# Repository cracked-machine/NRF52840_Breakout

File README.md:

### NRF52840 Breakout Board

Simple dev board for NRF52840 MCU, breaks out all pins to the board.

Antenna options to be confirmed.

#### Schematic

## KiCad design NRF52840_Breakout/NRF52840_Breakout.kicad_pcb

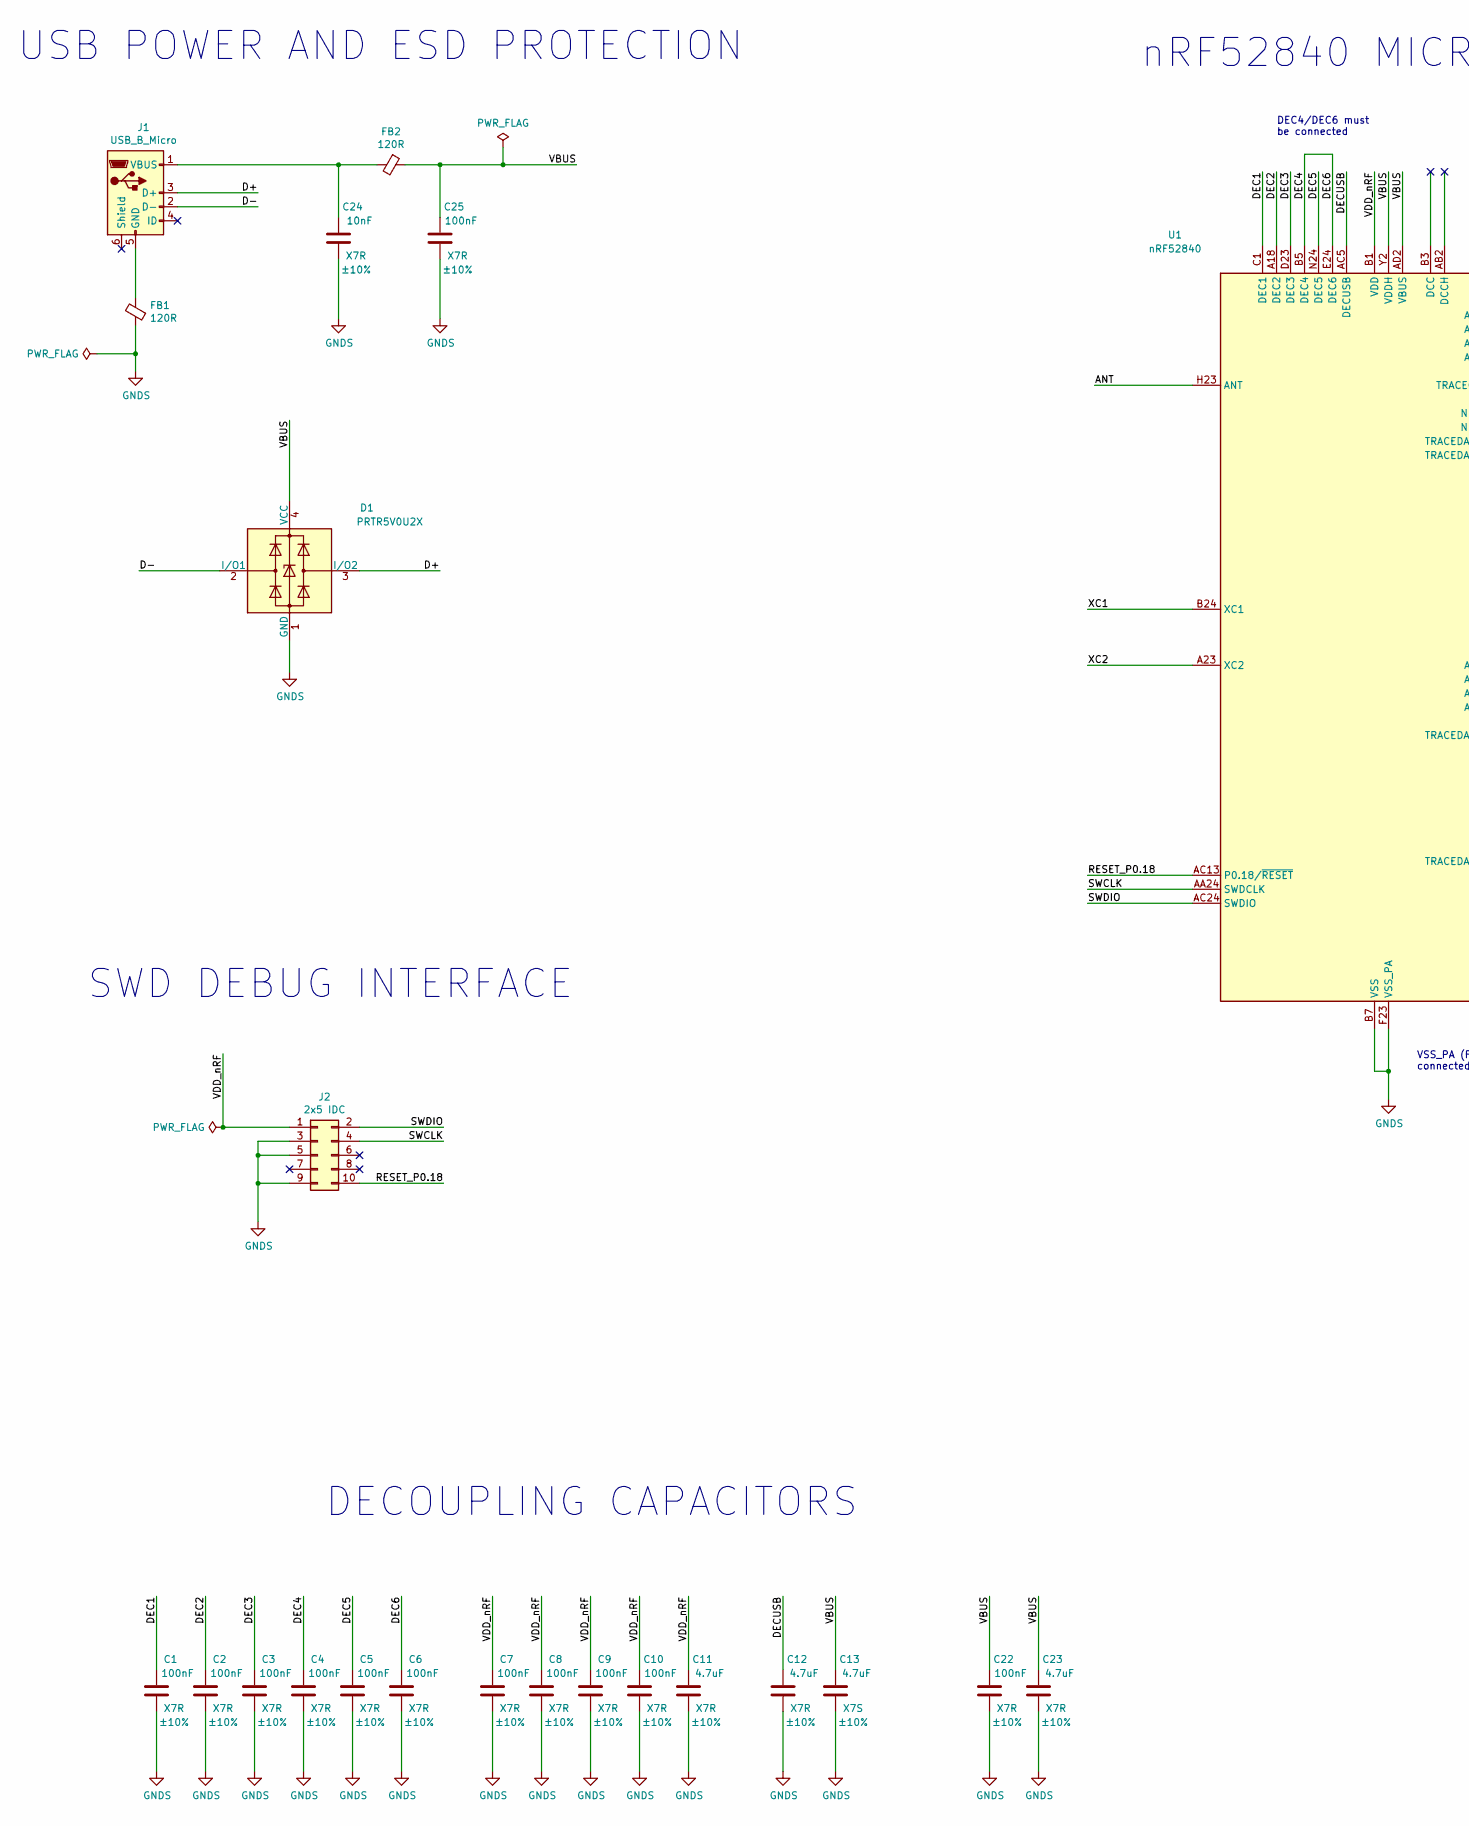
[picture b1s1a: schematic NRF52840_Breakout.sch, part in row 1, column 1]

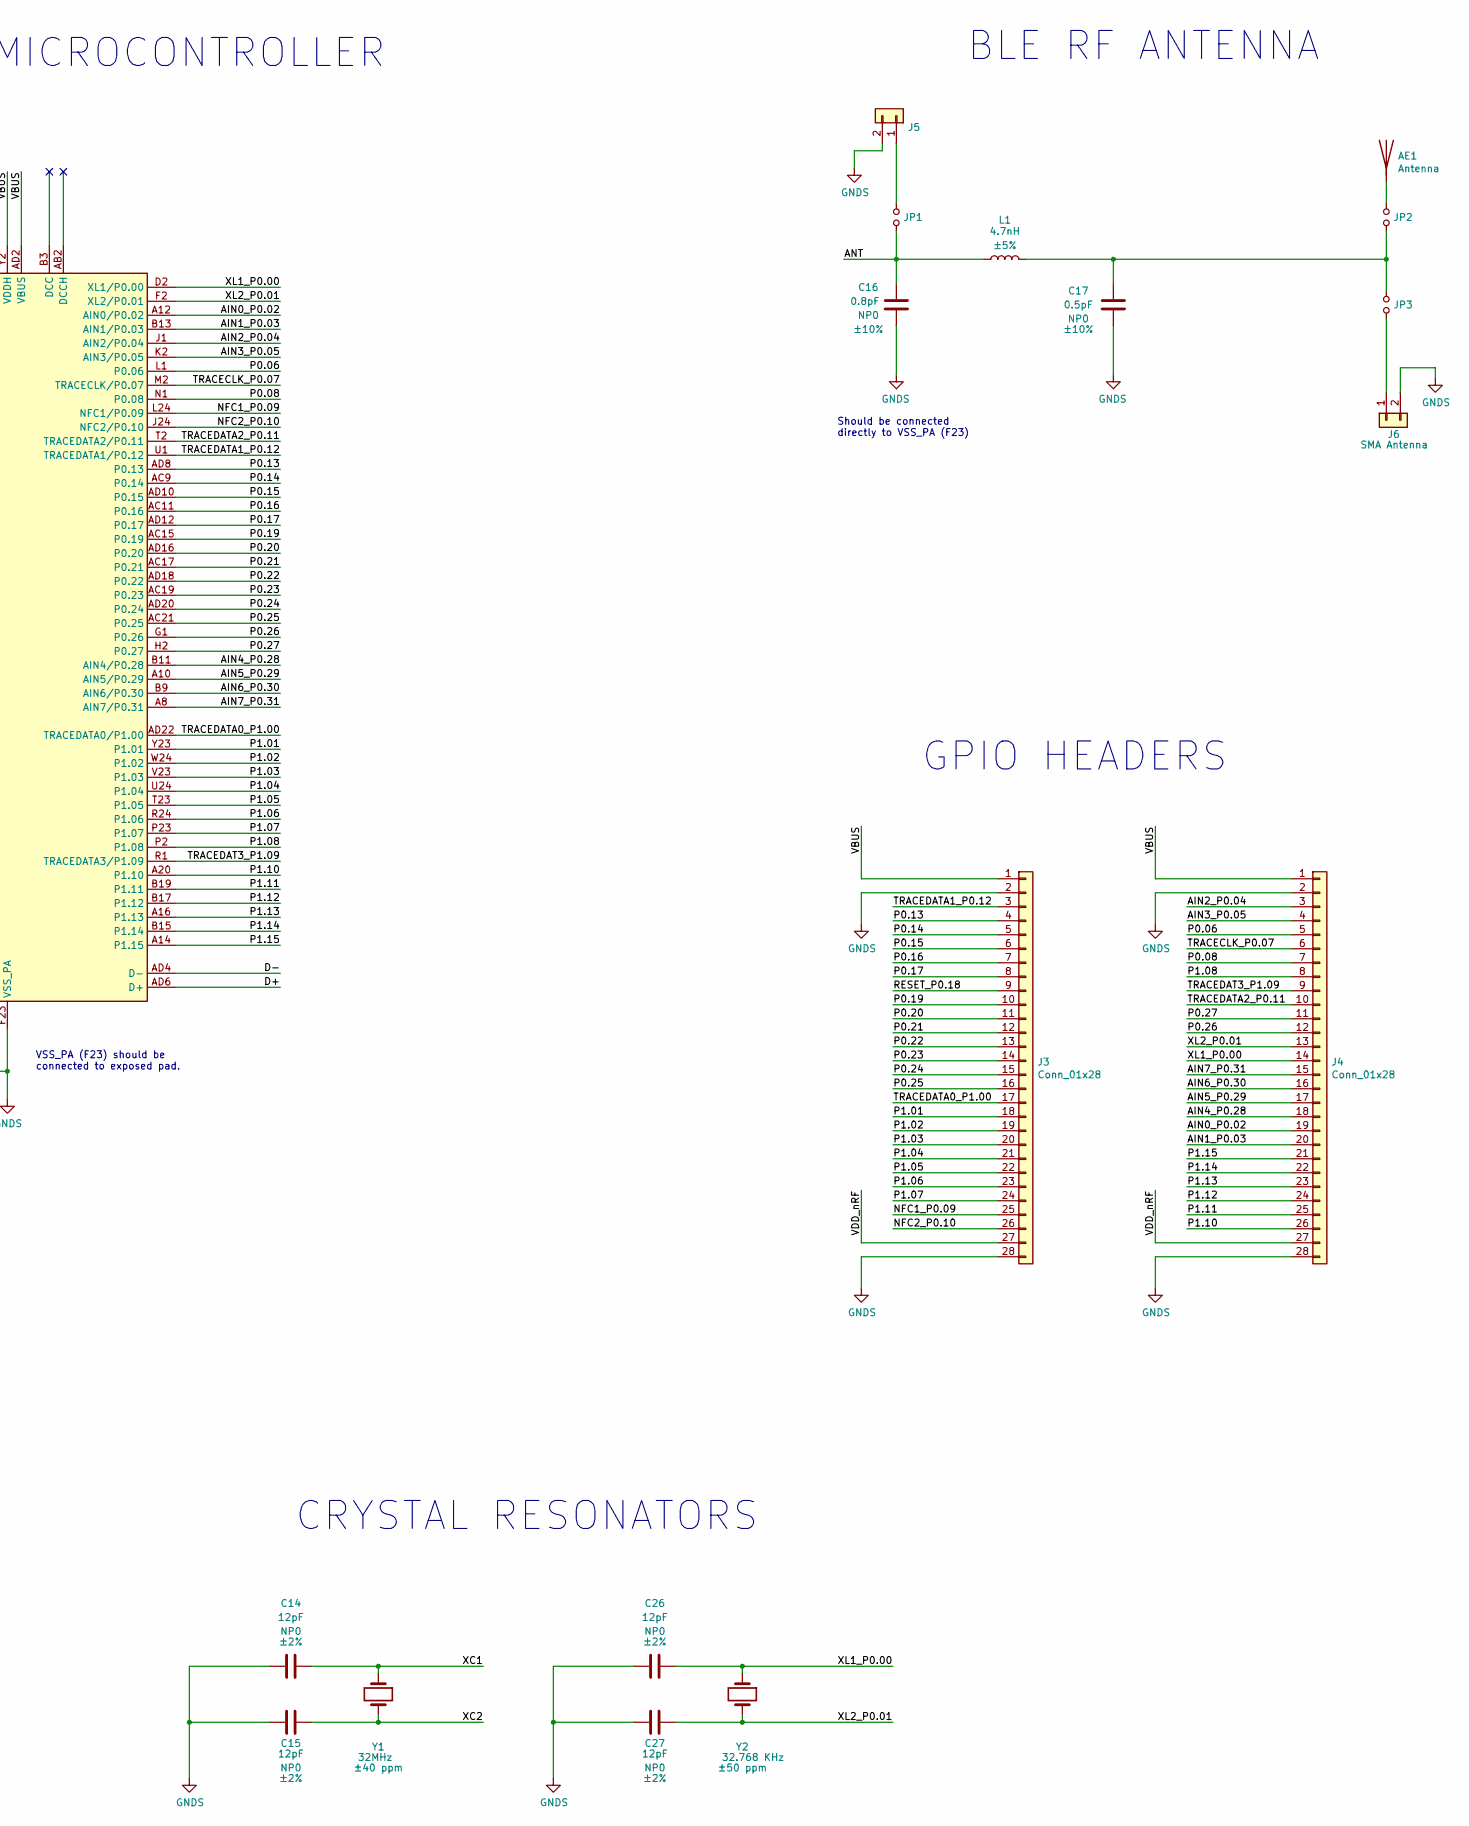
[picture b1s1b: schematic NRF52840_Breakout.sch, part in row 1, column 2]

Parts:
AE1: Antenna; Nordic_2_4GHz_Meander_RightSided
C1, C2, C3, C4, C5, C6, C7, C8, C9, C10, C22, C25: 100nF; C_0402_1005Metric_Pad0.74x0.62mm_HandSolder; Tolerance ±10%
C11, C12, C23: 4.7uF; C_0402_1005Metric_Pad0.74x0.62mm_HandSolder; Tolerance ±10%
C13: 4.7uF; C_0603_1608Metric_Pad1.08x0.95mm_HandSolder; Tolerance ±10%
C14, C15, C26, C27: 12pF; C_0402_1005Metric_Pad0.74x0.62mm_HandSolder; Tolerance ±2%
C16: 0.8pF; C_0402_1005Metric_Pad0.74x0.62mm_HandSolder; Tolerance ±10%
C17: 0.5pF; C_0402_1005Metric_Pad0.74x0.62mm_HandSolder; Tolerance ±10%
C24: 10nF; C_0402_1005Metric_Pad0.74x0.62mm_HandSolder; Tolerance ±10%
D1: PRTR5V0U2X; SOT-143
FB1, FB2: 120R; L_0402_1005Metric_Pad0.77x0.64mm_HandSolder
J1: USB_B_Micro; USB_Micro-B_Molex-105017-0001
J2: 2x5 IDC; PinHeader_2x05_P1.27mm_Vertical_SMD
J3, J4: Conn_01x28; PinHeader_1x28_P2.54mm_Vertical
J5: Conn_01x02; MMCX_Molex_73415-1471_Vertical
J6: SMA Antenna; MMCX_Molex_73415-1471_Vertical
JP1, JP2, JP3: Jumper_NO_Small; C_0402_1005Metric_Pad0.74x0.62mm_HandSolder
L1: 4.7nH; L_0402_1005Metric_Pad0.77x0.64mm_HandSolder; Tolerance ±5%
U1: nRF52840; Nordic_AQFN-73-1EP_7x7mm_P0.5mm
Y1: 32MHz; Crystal_SMD_2016-4Pin_2.0x1.6mm; Tolerance ±40 ppm
Y2: 32.768 KHz; Crystal_SMD_3215-2Pin_3.2x1.5mm; Tolerance ±50 ppm

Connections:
/AIN0_P0.02: J4.19, U1.A12 (AIN0/P0.02)
/AIN1_P0.03: J4.20, U1.B13 (AIN1/P0.03)
/AIN2_P0.04: J4.3, U1.J1 (AIN2/P0.04)
/AIN3_P0.05: J4.4, U1.K2 (AIN3/P0.05)
/AIN4_P0.28: J4.18, U1.B11 (AIN4/P0.28)
/AIN5_P0.29: J4.17, U1.A10 (AIN5/P0.29)
/AIN6_P0.30: J4.16, U1.B9 (AIN6/P0.30)
/AIN7_P0.31: J4.15, U1.A8 (AIN7/P0.31)
/ANT: C16.2, JP1.2, L1.2, U1.H23 (ANT)
/D+: D1.3 (I/O2), J1.3 (D+), U1.AD6 (D+)
/D-: D1.2 (I/O1), J1.2 (D-), U1.AD4 (D-)
/DEC1: C1.2, U1.C1 (DEC1)
/DEC2: C2.2, U1.A18 (DEC2)
/DEC3: C3.2, U1.D23 (DEC3)
/DEC4: C4.2, C6.2, U1.B5 (DEC4), U1.E24 (DEC6)
/DEC5: C5.2, U1.N24 (DEC5)
/DECUSB: C12.2, U1.AC5 (DECUSB)
/NFC1_P0.09: J3.25, U1.L24 (NFC1/P0.09)
/NFC2_P0.10: J3.26, U1.J24 (NFC2/P0.10)
/P0.06: J4.5, U1.L1 (P0.06)
/P0.08: J4.7, U1.N1 (P0.08)
/P0.13: J3.4, U1.AD8 (P0.13)
/P0.14: J3.5, U1.AC9 (P0.14)
/P0.15: J3.6, U1.AD10 (P0.15)
/P0.16: J3.7, U1.AC11 (P0.16)
/P0.17: J3.8, U1.AD12 (P0.17)
/P0.19: J3.10, U1.AC15 (P0.19)
/P0.20: J3.11, U1.AD16 (P0.20)
/P0.21: J3.12, U1.AC17 (P0.21)
/P0.22: J3.13, U1.AD18 (P0.22)
/P0.23: J3.14, U1.AC19 (P0.23)
/P0.24: J3.15, U1.AD20 (P0.24)
/P0.25: J3.16, U1.AC21 (P0.25)
/P0.26: J4.12, U1.G1 (P0.26)
/P0.27: J4.11, U1.H2 (P0.27)
/P1.01: J3.18, U1.Y23 (P1.01)
/P1.02: J3.19, U1.W24 (P1.02)
/P1.03: J3.20, U1.V23 (P1.03)
/P1.04: J3.21, U1.U24 (P1.04)
/P1.05: J3.22, U1.T23 (P1.05)
/P1.06: J3.23, U1.R24 (P1.06)
/P1.07: J3.24, U1.P23 (P1.07)
/P1.08: J4.8, U1.P2 (P1.08)
/P1.10: J4.26, U1.A20 (P1.10)
/P1.11: J4.25, U1.B19 (P1.11)
/P1.12: J4.24, U1.B17 (P1.12)
/P1.13: J4.23, U1.A16 (P1.13)
/P1.14: J4.22, U1.B15 (P1.14)
/P1.15: J4.21, U1.A14 (P1.15)
/RESET_P0.18: J2.10, J3.9, U1.AC13 (P0.18/~RESET)
/SWCLK: J2.4, U1.AA24 (SWDCLK)
/SWDIO: J2.2, U1.AC24 (SWDIO)
/TRACECLK_P0.07: J4.6, U1.M2 (TRACECLK/P0.07)
/TRACEDAT3_P1.09: J4.9, U1.R1 (TRACEDATA3/P1.09)
/TRACEDATA0_P1.00: J3.17, U1.AD22 (TRACEDATA0/P1.00)
/TRACEDATA1_P0.12: J3.3, U1.U1 (TRACEDATA1/P0.12)
/TRACEDATA2_P0.11: J4.10, U1.T2 (TRACEDATA2/P0.11)
/VBUS: C13.2, C22.2, C23.2, C25.2, D1.4 (VCC), FB2.1, J3.1, J4.1, U1.AD2 (VBUS), U1.Y2 (VDDH)
/VDD_nRF: C7.2, C8.2, C9.2, C10.2, C11.2, J2.1, J3.27, J4.27, U1.A22 (VDD), U1.AD14 (VDD), U1.AD23 (VDD), U1.B1 (VDD), U1.W1 (VDD)
/XC1: C14.1, U1.B24 (XC1), Y1.1
/XC2: C15.1, U1.A23 (XC2), Y1.2
/XL1_P0.00: C26.1, J4.14, U1.D2 (XL1/P0.00), Y2.1
/XL2_P0.01: C27.1, J4.13, U1.F2 (XL2/P0.01), Y2.2
GNDS: C1.1, C2.1, C3.1, C4.1, C5.1, C6.1, C7.1, C8.1, C9.1, C10.1, C11.1, C12.1, C13.1, C14.2, C15.2, C16.1, C17.1, C22.1, C23.1, C24.1, C25.1, C26.2, C27.2, D1.1 (GND), FB1.1, J2.3, J2.5, J2.9, J3.2, J3.28, J4.2, J4.28, J5.2, J6.2, U1.B7 (VSS), U1.EP (VSS), U1.F23 (VSS_PA)
unnamed: AE1.1, JP2.1
unnamed: C17.2, JP2.2, JP3.1, L1.1
unnamed: C24.2, FB2.2, J1.1 (VBUS)
unnamed: FB1.2, J1.5 (GND)
unnamed: J5.1, JP1.1
unnamed: J6.1, JP3.2

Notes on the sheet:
USB POWER AND ESD PROTECTION
SWD DEBUG INTERFACE
DECOUPLING CAPACITORS
CRYSTAL RESONATORS
GPIO HEADERS
BLE RF ANTENNA
nRF52840 MICROCONTROLLER
Should be connected directly to VSS_PA (F23)
VSS_PA (F23) should be connected to exposed pad.
DEC4/DEC6 must be connected

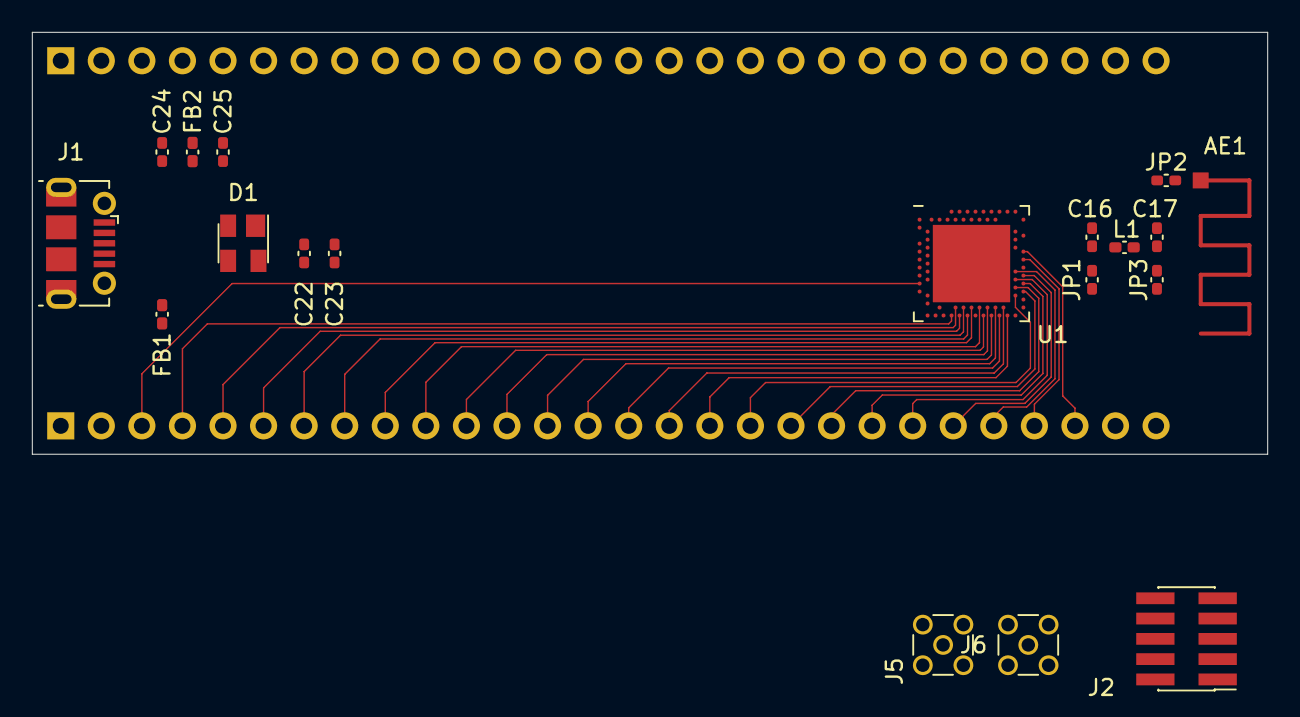
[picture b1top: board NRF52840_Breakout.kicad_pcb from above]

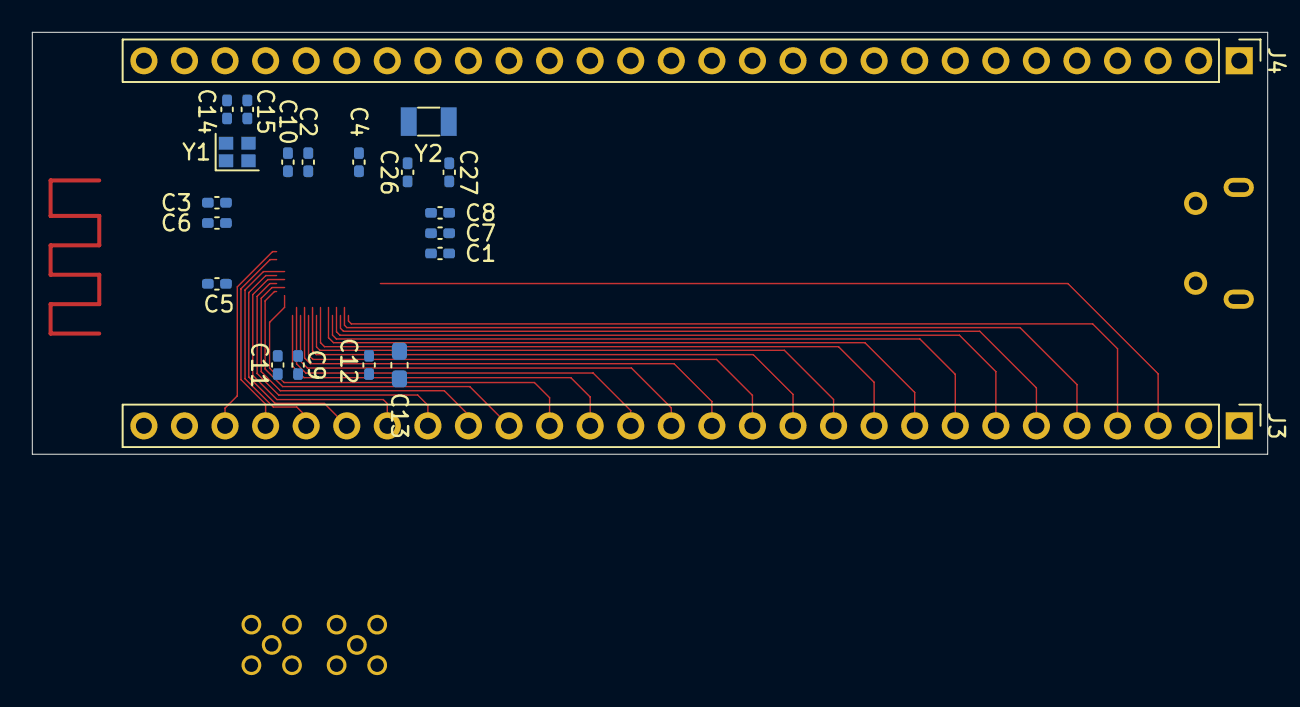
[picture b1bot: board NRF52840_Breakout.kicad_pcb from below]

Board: 4 copper layers, 77.3 x 26.4 mm, 40 parts (21 on the bottom side), 70 nets.

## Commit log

2021-03-08 Schematic RevA complete
2021-03-08 updated schema docs and readme
